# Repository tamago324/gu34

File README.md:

# gu34

horizon プラグインを使ってボトムプレートとトッププレートを生成した

## LICENSE

<br />この 作品 は <a rel="license" href="http://creativecommons.org/licenses/by-nc/4.0/">クリエイティブ・コモンズ 表示 - 非営利 4.0 国際 ライセンス</a>の下に提供されています。

> 表示 — あなたは 適切なクレジットを表示し、ライセンスへのリンクを提供し、変更があったらその旨を示さなければなりません。これらは合理的であればどのような方法で行っても構いませんが、許諾者があなたやあなたの利用行為を支持していると示唆するような方法は除きます。
>
> 非営利 — あなたは営利目的でこの資料を利用してはなりません。

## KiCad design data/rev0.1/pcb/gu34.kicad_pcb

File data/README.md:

# gu34

## 発注するためのデータの作り方

1. (horizon プラグイン)[https://github.com/skarrmann/horizon]を KiCAD に入れる
2. `revX` (`rev0.1` や `rev0.2` など) 内の `pcb/gu34.kicad_pcb` を開く
3. horizon プラグインを使って、発注するためのデータを作成する

## horizon プラグインの使い方

### もととなるKiCADのデータの作成方法

ボトムプレートとトッププレートを生成するためのデータはレイヤごとに作成されます

* `F.Adhesive` レイヤ：トッププレートの穴とEdge.Cuts
* `B.Adhesive` レイヤ：ボトムプレートの穴とEdge.Cuts

### horizon プラグインを使用して、ボトムプレートとトッププレートのデータを生成する

PCBエディタを開き、ツール > 外部プラグイン > Horizon Board Productor を実行する。

正しく実行できた場合、`data/` ディレクトリに `temp` と `gerbers` が生成される。

`temp` は KiCAD プロジェクトで、`gerbers` は JLCPCB (のみ？) に発注できるデータ。

`temp` を修正し、ガーバーファイルを生成して、発注することも可能

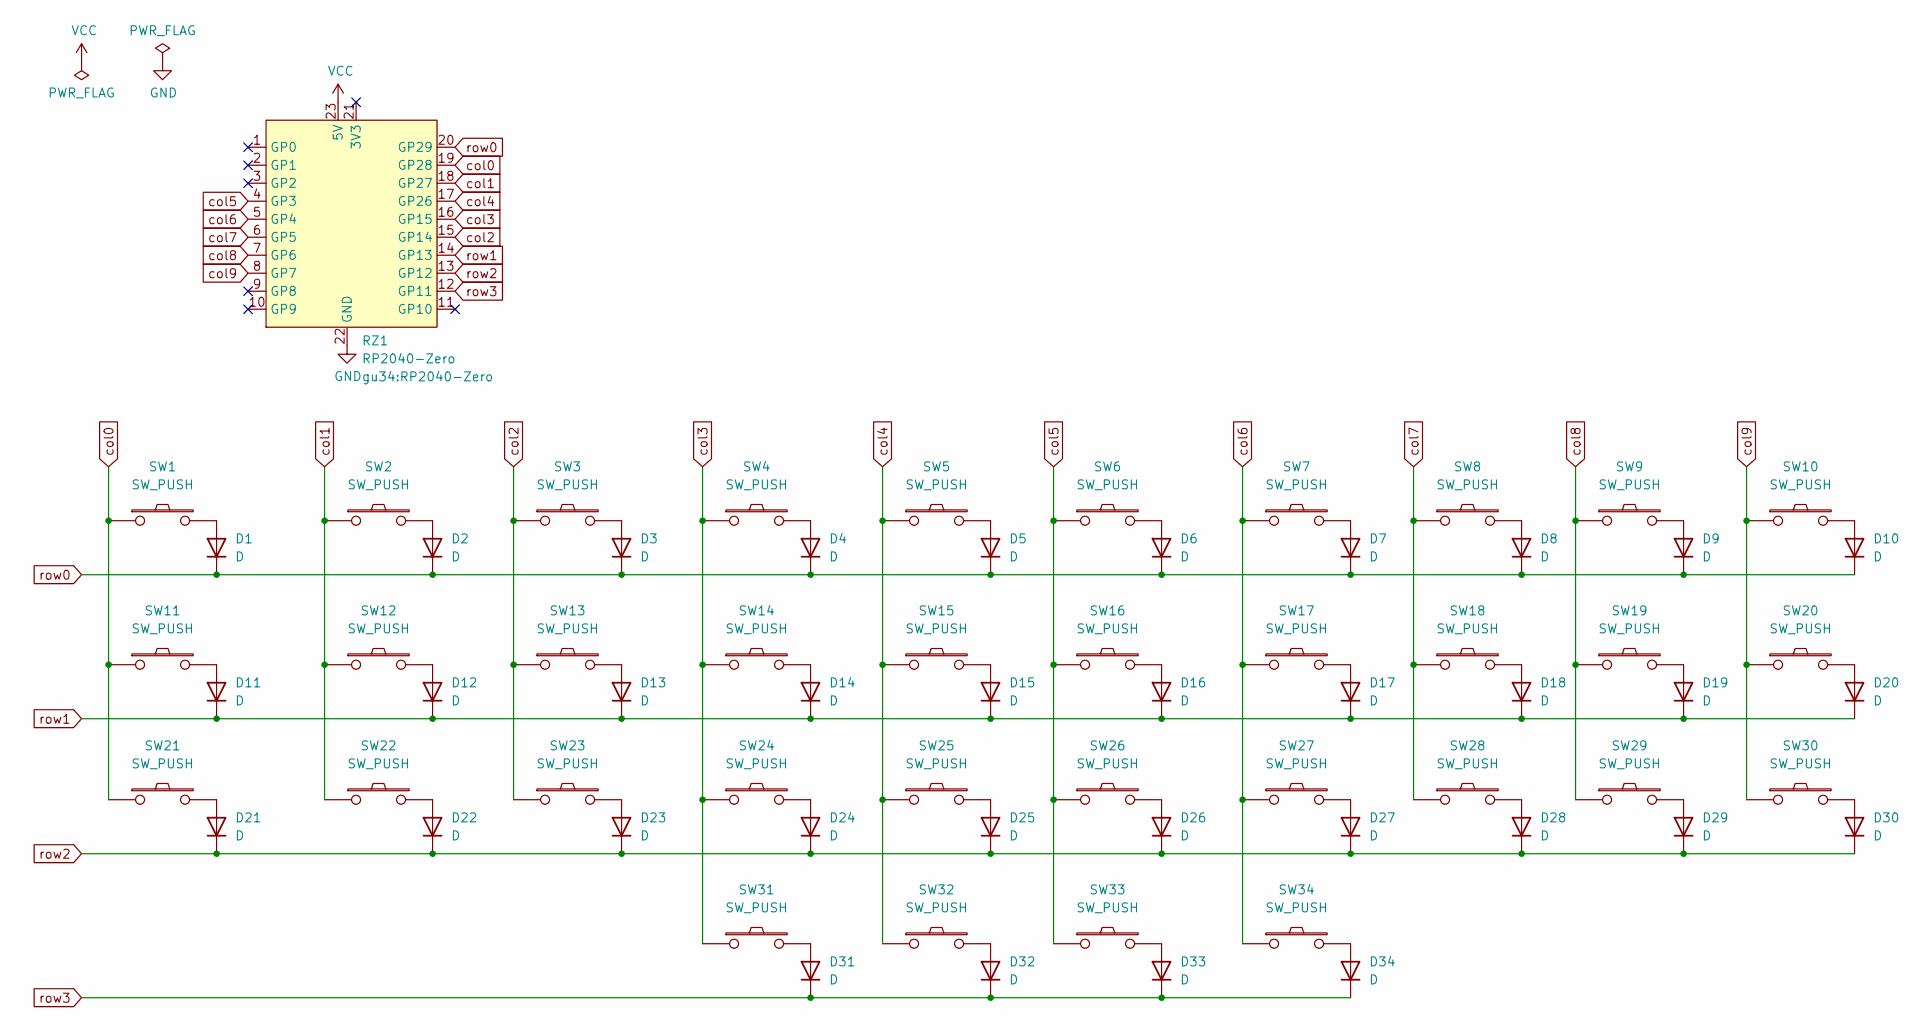
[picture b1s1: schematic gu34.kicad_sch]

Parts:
D1, D2, D3, D4, D5, D6, D7, D8, D9, D10, D11, D12, D13, D14, D15, D16, D17, D18, D19, D20, D21, D22, D23, D24, D25, D26, D27, D28, D29, D30, D31, D32, D33, D34: D; Diode_SMD
RZ1: RP2040-Zero
SW1, SW2, SW3, SW4, SW5, SW6, SW7, SW8, SW9, SW10, SW11, SW12, SW13, SW14, SW15, SW16, SW17, SW18, SW19, SW20, SW21, SW22, SW23, SW24, SW25, SW26, SW27, SW28, SW29, SW30, SW31, SW32, SW33, SW34: SW_PUSH; SW_Choc

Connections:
GND: RZ1.22 (GND)
unnamed: D1.2 (A), SW1.2
unnamed: D2.2 (A), SW2.2
unnamed: D3.2 (A), SW3.2
unnamed: D4.2 (A), SW4.2
unnamed: D5.2 (A), SW5.2
unnamed: D6.2 (A), SW6.2
unnamed: D7.2 (A), SW7.2
unnamed: D8.2 (A), SW8.2
unnamed: D9.2 (A), SW9.2
unnamed: D10.2 (A), SW10.2
unnamed: D11.2 (A), SW11.2
unnamed: D12.2 (A), SW12.2
unnamed: D13.2 (A), SW13.2
unnamed: D14.2 (A), SW14.2
unnamed: D15.2 (A), SW15.2
unnamed: D16.2 (A), SW16.2
unnamed: D17.2 (A), SW17.2
unnamed: D18.2 (A), SW18.2
unnamed: D19.2 (A), SW19.2
unnamed: D20.2 (A), SW20.2
unnamed: D21.2 (A), SW21.2
unnamed: D22.2 (A), SW22.2
unnamed: D23.2 (A), SW23.2
unnamed: D24.2 (A), SW24.2
unnamed: D25.2 (A), SW25.2
unnamed: D26.2 (A), SW26.2
unnamed: D27.2 (A), SW27.2
unnamed: D28.2 (A), SW28.2
unnamed: D29.2 (A), SW29.2
unnamed: D30.2 (A), SW30.2
unnamed: D31.2 (A), SW31.2
unnamed: D32.2 (A), SW32.2
unnamed: D33.2 (A), SW33.2
unnamed: D34.2 (A), SW34.2
VCC: RZ1.23 (5V)
col0: RZ1.19 (GP28), SW1.1, SW11.1, SW21.1
col1: RZ1.18 (GP27), SW2.1, SW12.1, SW22.1
col2: RZ1.15 (GP14), SW3.1, SW13.1, SW23.1
col3: RZ1.16 (GP15), SW4.1, SW14.1, SW24.1, SW31.1
col4: RZ1.17 (GP26), SW5.1, SW15.1, SW25.1, SW32.1
col5: RZ1.4 (GP3), SW6.1, SW16.1, SW26.1, SW33.1
col6: RZ1.5 (GP4), SW7.1, SW17.1, SW27.1, SW34.1
col7: RZ1.6 (GP5), SW8.1, SW18.1, SW28.1
col8: RZ1.7 (GP6), SW9.1, SW19.1, SW29.1
col9: RZ1.8 (GP7), SW10.1, SW20.1, SW30.1
row0: D1.1 (K), D2.1 (K), D3.1 (K), D4.1 (K), D5.1 (K), D6.1 (K), D7.1 (K), D8.1 (K), D9.1 (K), D10.1 (K), RZ1.20 (GP29)
row1: D11.1 (K), D12.1 (K), D13.1 (K), D14.1 (K), D15.1 (K), D16.1 (K), D17.1 (K), D18.1 (K), D19.1 (K), D20.1 (K), RZ1.14 (GP13)
row2: D21.1 (K), D22.1 (K), D23.1 (K), D24.1 (K), D25.1 (K), D26.1 (K), D27.1 (K), D28.1 (K), D29.1 (K), D30.1 (K), RZ1.13 (GP12)
row3: D31.1 (K), D32.1 (K), D33.1 (K), D34.1 (K), RZ1.12 (GP11)

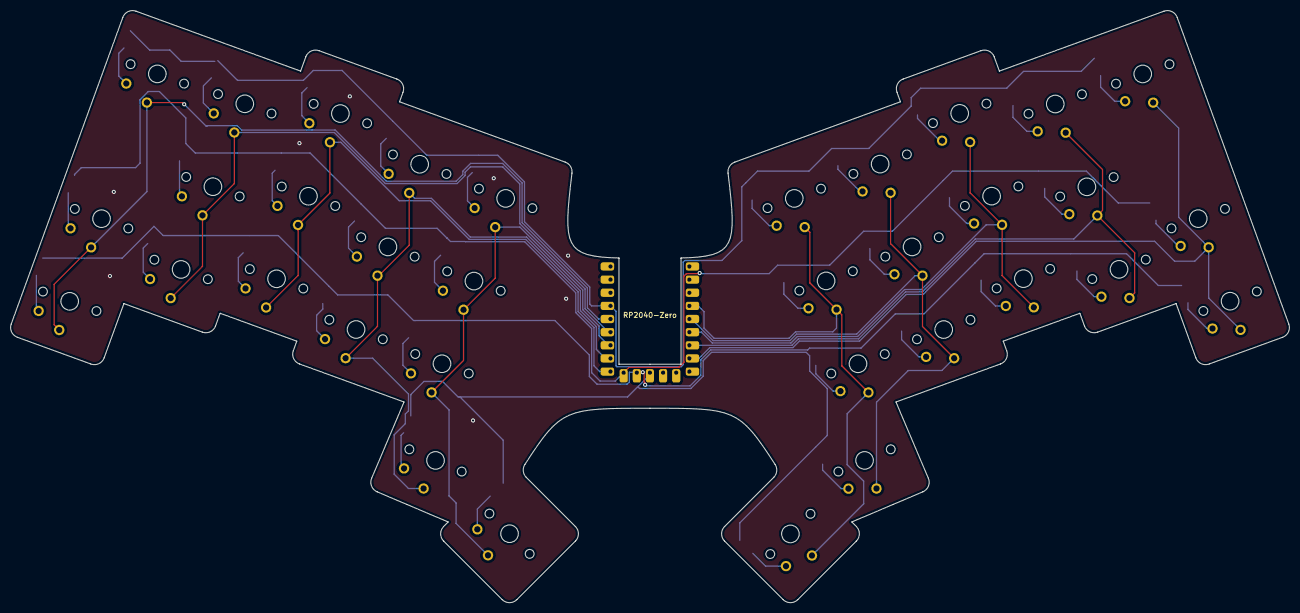
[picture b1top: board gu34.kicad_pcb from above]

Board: 2 copper layers, 247.2 x 114.5 mm, 69 parts (0 on the bottom side), 48 nets.

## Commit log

2023-05-10 init
2023-05-10 typo 修正
2023-05-16 rp2040 zero のフットプリントとシンボルが正しくなかったため、修正した
2023-05-18 update pic
2023-05-18 add top-plate

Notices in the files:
README.md:
LICENSE:
CC BY-NC 4.0
